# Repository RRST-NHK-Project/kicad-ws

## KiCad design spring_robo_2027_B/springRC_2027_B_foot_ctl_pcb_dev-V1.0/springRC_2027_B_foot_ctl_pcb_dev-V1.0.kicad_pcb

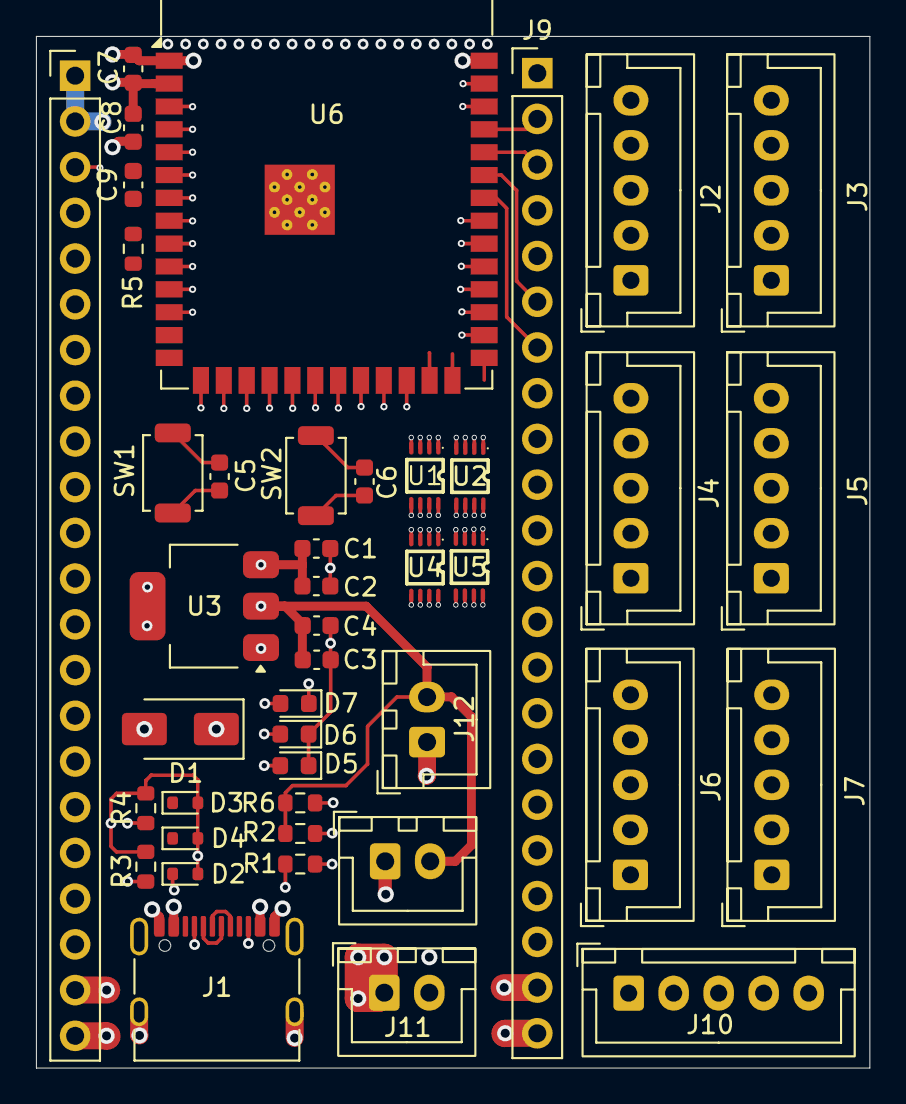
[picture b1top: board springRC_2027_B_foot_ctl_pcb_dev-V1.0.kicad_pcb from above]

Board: 4 copper layers, 46.3 x 57.3 mm, 43 parts (0 on the bottom side), 58 nets.

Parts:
C1, C3, C7: 10uF; C_0603_1608Metric
C2, C4, C5, C6, C8: 100nF; C_0603_1608Metric
C9: 1uF; C_0603_1608Metric
D1: SS14; D_SMA
D2, D3, D4: LESD5D5.0CT1G; D_SOD-523
D5, D6, D7: LED; LED_0603_1608Metric
J1: USB_C_Receptacle_USB2.0_16P; USB_C_Receptacle_XKB_U262-16XN-4BVC11
J2, J3, J4, J5, J6, J7, J10: Conn_01x05_Socket; JST_XH_B5B-XH-A_1x05_P2.50mm_Vertical
J8, J9: Conn_01x22_Pin; PinHeader_1x22_P2.54mm_Vertical
J11, J12, J13: Conn_01x02_Socket; JST_XH_B2B-XH-A_1x02_P2.50mm_Vertical
R1, R2: 5.1k; R_0603_1608Metric
R3, R4: 5.1K; R_0603_1608Metric
R5: 10k; R_0603_1608Metric
R6: 330; R_0603_1608Metric
SW1, SW2: SW_Push; SW_SPST_TS-1088-xR020
U1, U2, U4, U5: SN74LVC3G17DCUR; VSSOP-8_L2.1-W2.4-P0.50-LS3.2-BR
U3: LD1117S33TR_SOT223; SOT-223-3_TabPin2
U6: ESP32-S3-WROOM-1

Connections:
3V3: C3.2, C4.2, C7.1, C8.1, J8.1, J8.2, J12.2, J13.2, R2.1, R5.1, R6.2, U1.8 (VCC), U2.8 (VCC), U3.2 (VO), U4.8 (VCC), U5.8 (VCC), U6.2 (3V3)
+5V: C1.1, C2.1, D1.1 (K), J2.2, J3.2, J4.2, J5.2, J8.21, J11.2, R1.1, U3.3 (VI)
DN: D3.1, J1.A7 (D-), J1.B7 (D-), J9.20, U6.13 (USB_D-)
DP: D4.1, J1.A6 (D+), J1.B6 (D+), J9.19, U6.14 (USB_D+)
EN: C5.1, C9.1, J8.3, R5.2, SW1.2, U6.3 (EN)
ENC1_A: J2.3, U1.1 (1A)
ENC1_A_BUF: J9.4, U1.7 (1Y), U6.39 (IO1)
ENC1_B: J2.1, U1.3 (2A)
ENC1_B_BUF: J9.5, U1.5 (2Y), U6.38 (IO2)
ENC1_X: J2.4, U1.6 (3A)
ENC1_X_BUF: J9.6, U1.2 (3Y), U6.35 (IO42)
ENC2_A: J3.3, U2.1 (1A)
ENC2_A_BUF: J9.7, U2.7 (1Y), U6.34 (IO41)
ENC2_B: J3.1, U2.3 (2A)
ENC2_B_BUF: J9.8, U2.5 (2Y), U6.33 (IO40)
ENC2_X: J3.4, U2.6 (3A)
ENC2_X_BUF: J9.9, U2.2 (3Y), U6.32 (IO39)
ENC3_A: J4.3, U4.1 (1A)
ENC3_A_BUF: J9.16, U4.7 (1Y), U6.25 (IO48)
ENC3_B: J4.1, U4.3 (2A)
ENC3_B_BUF: J9.17, U4.5 (2Y), U6.24 (IO47)
ENC3_X: J4.4, U4.6 (3A)
ENC3_X_BUF: J9.18, U4.2 (3Y), U6.23 (IO21)
ENC4_A: J5.3, U5.1 (1A)
ENC4_A_BUF: J8.4, U5.7 (1Y), U6.4 (IO4)
ENC4_B: J5.1, U5.3 (2A)
ENC4_B_BUF: J8.5, U5.5 (2Y), U6.5 (IO5)
ENC4_X: J5.4, U5.6 (3A)
ENC4_X_BUF: J8.6, U5.2 (3Y), U6.6 (IO6)
GND: C1.2, C2.2, C3.1, C4.1, C5.2, C6.2, C7.2, C8.2, C9.2, D2.2, D3.2, D4.2, D5.1 (K), D6.1 (K), J1.A1 (GND), J1.A12 (GND), J1.B1 (GND), J1.B12 (GND), J2.5, J3.5, J4.5, J5.5, J6.1, J7.1, J8.22, J9.1, J9.21, J9.22, J11.1, J12.1, J13.1, R3.2, R4.2, SW1.1, SW2.1, U1.4 (GND), U2.4 (GND), U3.1 (GND), U4.4 (GND), U5.4 (GND), U6.1 (GND), U6.40 (GND), U6.41 (GND)
IO0: C6.1, D7.1 (K), J9.14, SW2.2, U6.27 (IO0)
IO3: J8.13, U6.15 (IO3)
IO7: J8.7, J10.1, U6.7 (IO7)
IO8: J8.12, J10.2, U6.12 (IO8)
IO9: J7.4, J8.15, U6.17 (IO9)
IO10: J7.5, J8.16, U6.18 (IO10)
IO11: J7.2, J8.17, U6.19 (IO11)
IO12: J7.3, J8.18, U6.20 (IO12)
IO13: J8.19, J10.3, U6.21 (IO13)
IO14: J8.20, J10.4, U6.22 (IO14)
IO15: J6.4, J8.8, U6.8 (IO15)
IO16: J6.5, J8.9, U6.9 (IO16)
IO17: J6.3, J8.10, U6.10 (IO17)
IO18: J6.2, J8.11, U6.11 (IO18)
IO35: J9.13, U6.28 (IO35)
IO36: J9.12, U6.29 (IO36)
IO37: J9.11, U6.30 (IO37)
IO38: J9.10, J10.5, U6.31 (IO38)
IO45: J9.15, U6.26 (IO45)
IO46: J8.14, U6.16 (IO46)
unnamed: D5.2 (A), R1.2
unnamed: D6.2 (A), R2.2
unnamed: D7.2 (A), R6.1
unnamed: J1.A5 (CC1), R4.1
unnamed: J1.B5 (CC2), R3.1
RXD0: J9.3, U6.36 (RXD0)
TXD0: J9.2, U6.37 (TXD0)
VBUS: D1.2 (A), D2.1, J1.A4 (VBUS), J1.A9 (VBUS), J1.B4 (VBUS), J1.B9 (VBUS)
